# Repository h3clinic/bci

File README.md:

# BioGENEius Neural Signal Analysis Pipeline

## Model Details

| Field | Value |
|-------|-------|
| **Name** | BioGENEius Computational Pipeline v1 |
| **Version** | 1.0.0 |
| **Architecture** | Two-stage: Classical (CUSUM/RF) + Deep (NeuralQANet) |
| **Parameters** | 76,045 (Deep model) |
| **Framework** | PyTorch (CPU-only, no GPU required) |
| **License** | Research use only |

## Framing

> Artifact-resilient detection of suppression-like electrophysiological
> perturbation signatures under a low-cost phantom protocol.

**Key constraint:** We never claim neurons until we have biology.

## Intended Use

Detection and classification of electrophysiological perturbation signatures
in multichannel time-series data acquired from a low-cost phantom system.
Designed for competition demonstration and research prototyping.

### Primary Use Cases
- Detecting onset of suppression-like perturbations in phantom recordings
- Classifying perturbation cause (9 synthetic proxy classes)
- Quantifying detection latency and classification confidence
- Generating reproducible evaluation reports

### Out of Scope
- Clinical diagnosis or treatment decisions
- Real-time closed-loop neural interfaces
- Claims about biological neurotoxicity from proxy labels

## Pipeline Architecture

```
Acquire (frames → ADC → µV)
  ↓
QC / Artifact Segmentation (ML mask + quality score)
  ↓
Detect Change (CUSUM or z-score baseline comparison)
  ↓
Classify Cause (RF vs Deep model, 9-class + binary)
  ↓
Report (figures + latency + CI + confidence + "unknown" option)
```

### Stage 1 — Classical Detection
- **CUSUM** change-point detection on channel-averaged RMS
- **Z-score** alternative with sliding baseline window
- Outputs: detected (bool), detection latency (seconds), CUSUM statistic

### Stage 2 — Classical Classification
- **Random Forest** on 20 handcrafted features (RMS ratio, spectral entropy, band powers, etc.)
- Binary (perturbation vs baseline) + 9-class cause classification
- Wilson confidence intervals on all accuracy metrics

### Stage 3 — Deep Classification (NeuralQANet)
- 1D CNN backbone → attention pooling → 3 heads:
  - Artifact mask (binary per-sample)
  - Cause classification (9-class)
  - Severity regression (continuous 0–1)
- Self-supervised pretraining: masked reconstruction + NT-Xent contrastive loss
- 7 domain-randomization augmentations: 60Hz injection, channel dropout, gain jitter, coupling, drift, clipping, time mask
- Temperature-calibrated output probabilities

## Proxy Labels — What We Claim and What We Don't

All perturbation classes are **proxy signatures†**, not validated biological effects:

| Class | Proxy Signature | What It Actually Is |
|-------|-----------------|---------------------|
| Spike Suppression† | Reduced spike amplitude/rate | Synthetic amplitude modulation |
| Burst Collapse† | Loss of burst patterns | Synthetic burst removal |
| Spectral Shift† | Changed power spectrum | Synthetic PSD warping |
| Mixed Suppression† | Combined signatures | Multiple synthetic effects |
| Amplitude Modulation† | Gain changes | Synthetic scaling |
| Frequency Drift† | Center frequency shift | Synthetic frequency modulation |
| Baseline Drift† | DC offset wander | Synthetic drift injection |
| Coupling Change† | Inter-channel correlation shift | Synthetic coupling matrix |
| Artifact Injection† | Non-physiological transient | Synthetic artifact waveforms |

**†** = proxy label. Biological validation requires phantom recordings
with known perturbation agents under controlled conditions.

## Training Data

- **Source**: `analysis/perturbation_library.py` — deterministic synthetic generators
- **Classes**: 9 perturbation types + baseline
- **Severities**: 3 levels (0.3, 0.6, 0.9)
- **Channels**: 16 (configurable)
- **Sample rate**: 20 kHz (configurable)
- **Augmentations**: 7 domain-randomization transforms

**No real biological data was used for training or evaluation.**

## Evaluation Protocol

| Figure | What It Tests |
|--------|--------------|
| Fig 1 | Onset detection latency + false positive rate |
| Fig 2 | Cause classification confusion matrix + ROC |
| Fig 3 | Robustness under noise and artifact stress |
| Fig 4 | Ablation — why two-stage matters |
| Fig 5 | 3-way comparison: Classical vs RF vs Deep |
| Fig 6 | Stress grid: SNR × severity (where Deep beats Classical) |
| Fig 7 | Domain shift: train A / test B generalization |

### ML Earns Its Keep
- **Random noise floor**: ML does NOT beat physics. PCB shielding + analog design does.
- **Structured artifacts**: ML DOES help with 60Hz, coupling, drift, and other patterned contamination.
- Deep model must beat RF baseline to be included; RF must beat CUSUM to be included.

## Known Limitations

1. **Synthetic only** — All training/evaluation on synthetic perturbation library. No real data yet.
2. **Domain shift** — Performance may degrade when real phantom data differs from synthetic assumptions.
3. **Small model** — 76K params is deliberately small for CPU inference; may under-fit complex patterns.
4. **Temperature calibration** — Calibrated on synthetic validation set; re-calibrate on real data.
5. **Proxy labels** — No biological ground truth. Labels describe electrical signatures, not mechanisms.
6. **Single phantom protocol** — Validated only against BioGENEius Phantom Protocol v2.

## "Unknown" Behavior

When the model encounters data that doesn't match any trained class:
- Top-class probability drops below 0.3
- System flags as "low-confidence" in predictions.csv
- **Intended behavior: don't make a call when you don't know**

## Reproducibility

```bash
# One command. Generates everything.
python analysis/run_pipeline.py --source synthetic --seed 42

# Outputs to out/run_YYYYMMDD_HHMMSS/:
#   fig1–fig7 (PNG), predictions.csv, metrics.json, model_card.md
```

All random state is seeded. Same seed → same results.

## Ethical Considerations

- This system processes synthetic electrical signals, not human data
- No patient data, no clinical decisions, no diagnostic claims
- Proxy labels are clearly marked to prevent over-interpretation
- "Unknown" class prevents forced classification of novel patterns
- All code and evaluation are fully reproducible and auditable

## Citation

If referencing this work, please cite the BioGENEius competition entry
and note that all results are from synthetic simulation studies.

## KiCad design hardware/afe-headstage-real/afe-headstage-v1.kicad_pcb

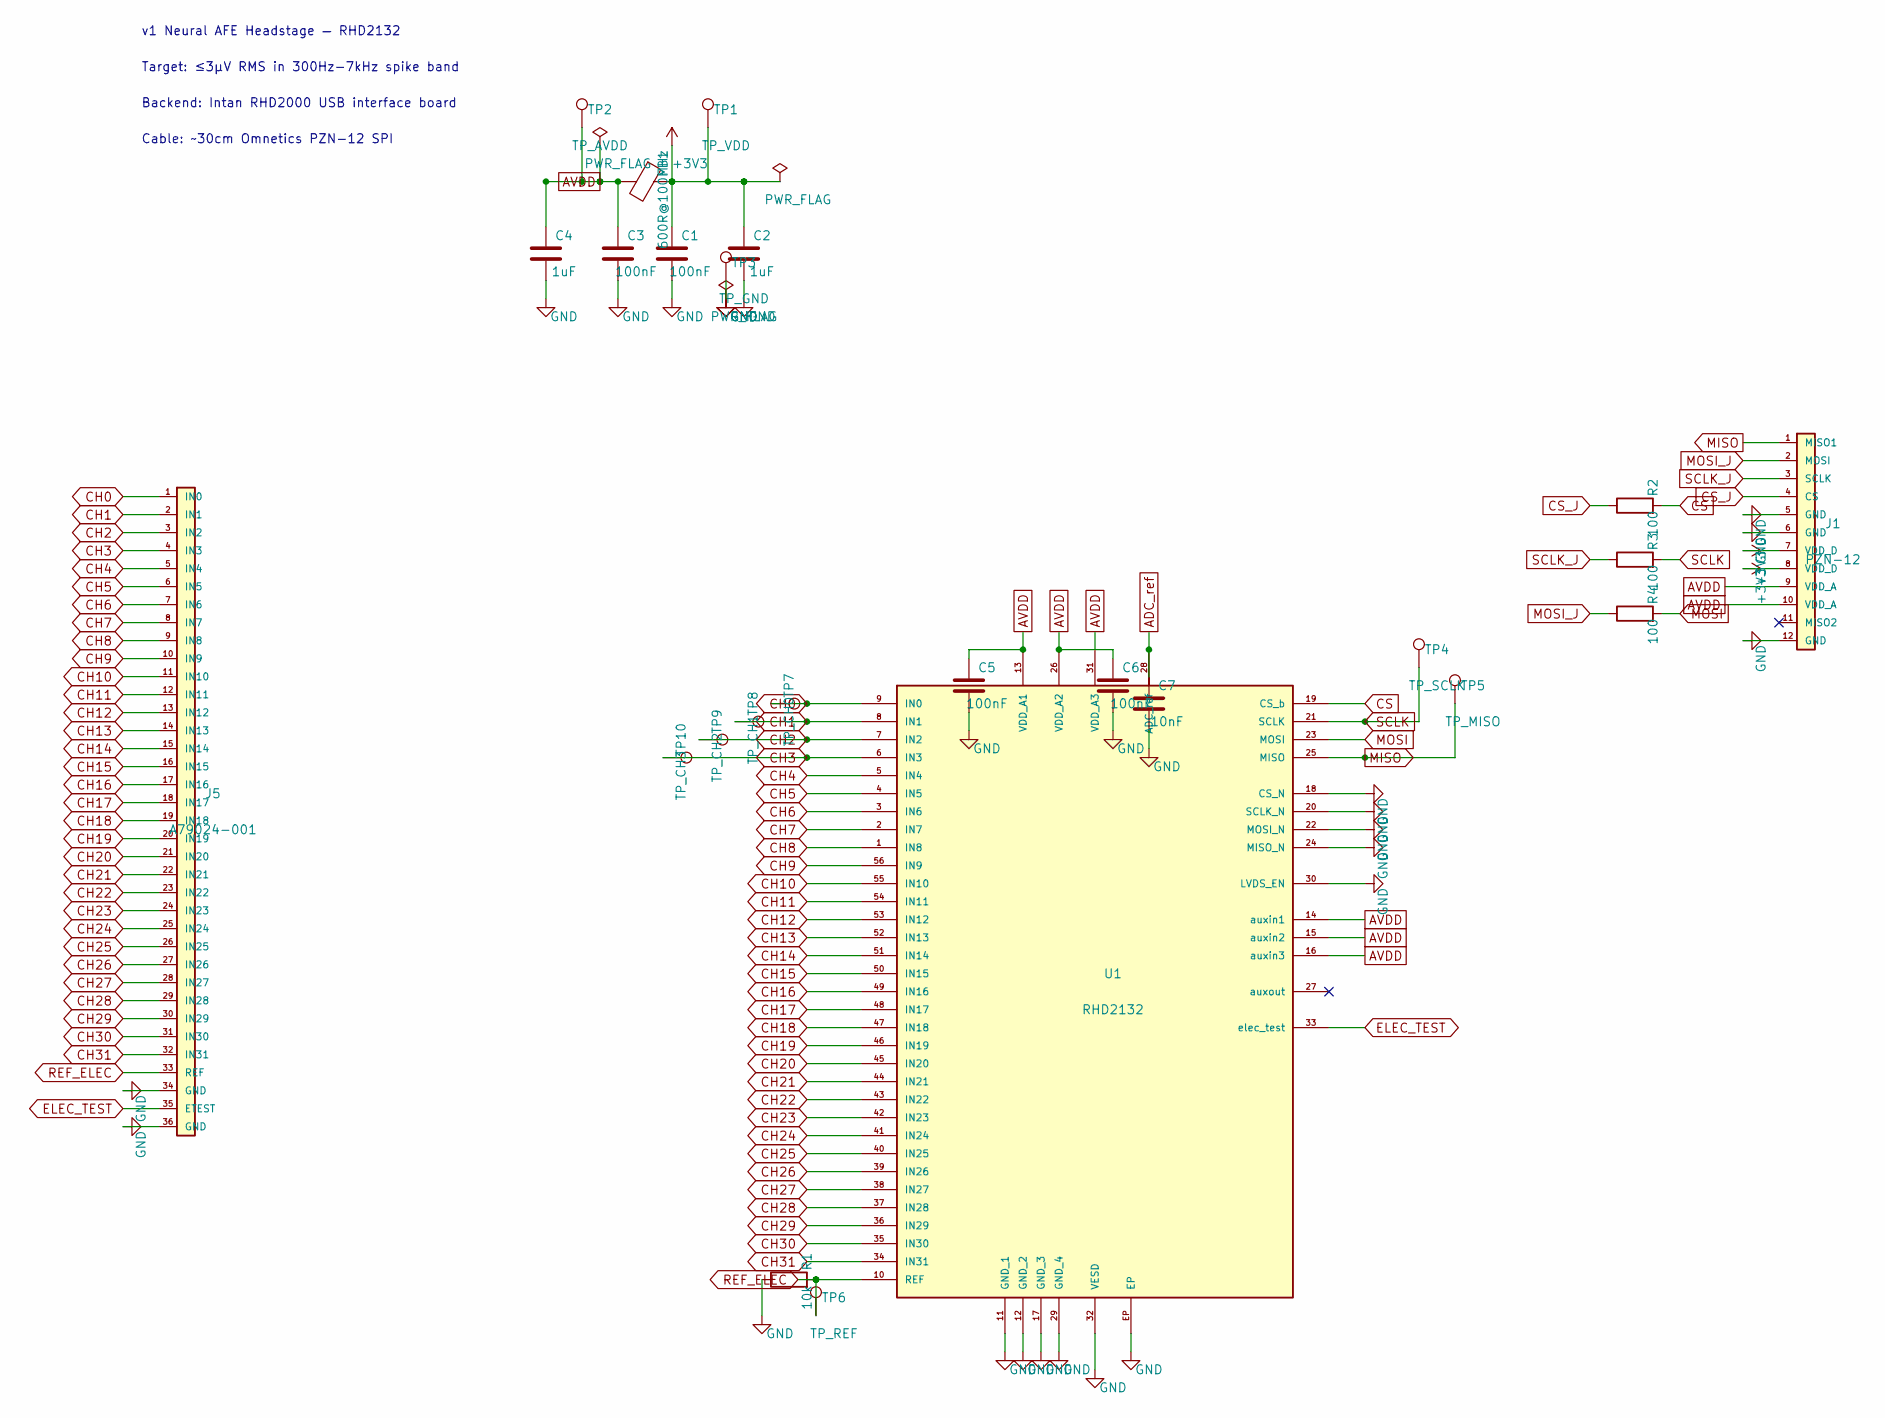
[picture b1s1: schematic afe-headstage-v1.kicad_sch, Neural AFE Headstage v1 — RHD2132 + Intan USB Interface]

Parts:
C1, C3, C5, C6: 100nF; R_0402_1005Metric
C2, C4: 1uF; R_0402_1005Metric
C7: 10nF; R_0402_1005Metric
FB1: 600R@100MHz; R_0402_1005Metric
J1: PZN-12; Omnetics_PZN-12-AA
J5: A79024-001; Omnetics_A79024_36pin
R1: 10k; R_0402_1005Metric
R2, R3, R4: 100; R_0402_1005Metric
TP1: TP_VDD; TestPoint_Pad_D1.0mm
TP2: TP_AVDD; TestPoint_Pad_D1.0mm
TP3: TP_GND; TestPoint_Pad_D1.0mm
TP4: TP_SCLK; TestPoint_Pad_D1.0mm
TP5: TP_MISO; TestPoint_Pad_D1.0mm
TP6: TP_REF; TestPoint_Pad_D1.0mm
TP7: TP_CH0; TestPoint_Pad_D1.0mm
TP8: TP_CH1; TestPoint_Pad_D1.0mm
TP9: TP_CH2; TestPoint_Pad_D1.0mm
TP10: TP_CH3; TestPoint_Pad_D1.0mm
U1: RHD2132; RHD2132_QFN56

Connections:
+3V3: C1.1, C2.1, FB1.1, J1.7 (VDD_D), J1.8 (VDD_D), TP1.1
ADC_ref: C7.1, U1.28 (ADC_ref)
AVDD: C3.1, C4.1, C5.1, C6.1, FB1.2, J1.9 (VDD_A), J1.10 (VDD_A), TP2.1, U1.13 (VDD_A1), U1.14 (auxin1), U1.15 (auxin2), U1.16 (auxin3), U1.26 (VDD_A2), U1.31 (VDD_A3)
CH0: J5.1 (IN0), TP7.1, U1.9 (IN0)
CH1: J5.2 (IN1), TP8.1, U1.8 (IN1)
CH2: J5.3 (IN2), TP9.1, U1.7 (IN2)
CH3: J5.4 (IN3), TP10.1, U1.6 (IN3)
CH4: J5.5 (IN4), U1.5 (IN4)
CH5: J5.6 (IN5), U1.4 (IN5)
CH6: J5.7 (IN6), U1.3 (IN6)
CH7: J5.8 (IN7), U1.2 (IN7)
CH8: J5.9 (IN8), U1.1 (IN8)
CH9: J5.10 (IN9), U1.56 (IN9)
CH10: J5.11 (IN10), U1.55 (IN10)
CH11: J5.12 (IN11), U1.54 (IN11)
CH12: J5.13 (IN12), U1.53 (IN12)
CH13: J5.14 (IN13), U1.52 (IN13)
CH14: J5.15 (IN14), U1.51 (IN14)
CH15: J5.16 (IN15), U1.50 (IN15)
CH16: J5.17 (IN16), U1.49 (IN16)
CH17: J5.18 (IN17), U1.48 (IN17)
CH18: J5.19 (IN18), U1.47 (IN18)
CH19: J5.20 (IN19), U1.46 (IN19)
CH20: J5.21 (IN20), U1.45 (IN20)
CH21: J5.22 (IN21), U1.44 (IN21)
CH22: J5.23 (IN22), U1.43 (IN22)
CH23: J5.24 (IN23), U1.42 (IN23)
CH24: J5.25 (IN24), U1.41 (IN24)
CH25: J5.26 (IN25), U1.40 (IN25)
CH26: J5.27 (IN26), U1.39 (IN26)
CH27: J5.28 (IN27), U1.38 (IN27)
CH28: J5.29 (IN28), U1.37 (IN28)
CH29: J5.30 (IN29), U1.36 (IN29)
CH30: J5.31 (IN30), U1.35 (IN30)
CH31: J5.32 (IN31), U1.34 (IN31)
CS: R2.2, U1.19 (CS_b)
CS_J: J1.4 (CS), R2.1
ELEC_TEST: J5.35 (ETEST), U1.33 (elec_test)
GND: C1.2, C2.2, C3.2, C4.2, C5.2, C6.2, C7.2, J1.5 (GND), J1.6 (GND), J1.12 (GND), J5.34 (GND), J5.36 (GND), R1.1, TP3.1, U1.11 (GND_1), U1.12 (GND_2), U1.17 (GND_3), U1.18 (CS_N), U1.20 (SCLK_N), U1.22 (MOSI_N), U1.24 (MISO_N), U1.29 (GND_4), U1.30 (LVDS_EN), U1.32 (VESD), U1.EP
MISO: J1.1 (MISO1), TP5.1, U1.25 (MISO)
MOSI: R4.2, U1.23 (MOSI)
MOSI_J: J1.2 (MOSI), R4.1
REF_ELEC: J5.33 (REF), R1.2, TP6.1, U1.10 (REF)
SCLK: R3.2, TP4.1, U1.21 (SCLK)
SCLK_J: J1.3 (SCLK), R3.1

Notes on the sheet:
v1 Neural AFE Headstage — RHD2132
Target: ≤3µV RMS in 300Hz-7kHz spike band
Backend: Intan RHD2000 USB interface board
Cable: ~30cm Omnetics PZN-12 SPI

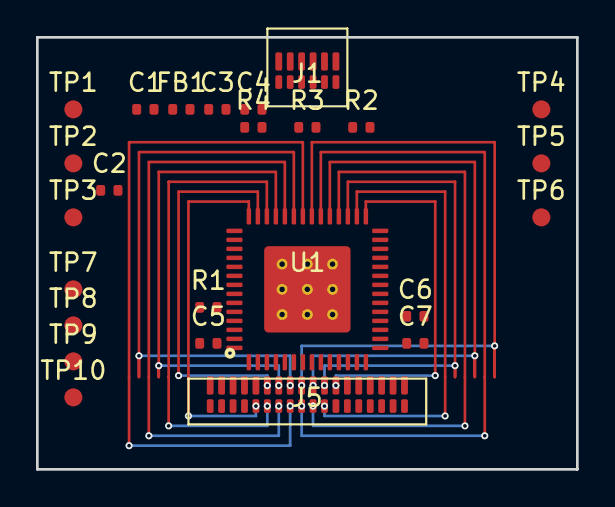
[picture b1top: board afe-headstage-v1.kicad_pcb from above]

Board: 4 copper layers, 30.0 x 24.0 mm, 25 parts (0 on the bottom side), 45 nets.

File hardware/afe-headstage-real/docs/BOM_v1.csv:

Ref,Qty,Value,Package,Description,MPN,Supplier,Notes
U1,1,RHD2132,QFN-56 (8x8mm),32-ch neural AFE with on-chip ADC,RHD2132,Intan Technologies,0.5mm pitch; EP 4.8x4.8mm; CMOS SPI mode
J1,1,PZN-12-AA,Omnetics PZN-12,"12-pin polarized nano, SPI cable connector",PZN-12-AA,Omnetics,Mates with Intan RHD2000 USB interface board cable
J5,1,A79024-001,Omnetics A79024,"36-pin nano-strip, electrode connector",A79024-001,Omnetics,0.635mm pitch; dual-row SMD
FB1,1,600R@100MHz,0402,Ferrite bead for analog supply filtering,BLM15AG601SN1D,Murata,AVDD/DVDD isolation
C1,1,100nF,0402,+3V3 bypass (near power entry),GRM155R71C104KA88D,Murata,X7R 16V
C2,1,1uF,0402,+3V3 bulk (near power entry),GRM155R61A105KE01D,Murata,X5R 10V
C3,1,100nF,0402,AVDD bypass (near FB1 output),GRM155R71C104KA88D,Murata,X7R 16V
C4,1,1uF,0402,AVDD bulk (near FB1 output),GRM155R61A105KE01D,Murata,X5R 10V
C5,1,100nF,0402,VDD bypass near U1 pin 13,GRM155R71C104KA88D,Murata,X7R 16V; <1mm from VDD1
C6,1,100nF,0402,VDD bypass near U1 pin 26,GRM155R71C104KA88D,Murata,X7R 16V; <1mm from VDD2
C7,1,10nF,0402,ADC_ref decoupling,GRM155R71H103KA88D,Murata,X7R 50V; <5mm from U1 pin 28
R1,1,10k,0402,REF electrode bias to GND,RC0402FR-0710KL,Yageo,1% tolerance
R2,1,100R,0402,SPI series — CS line,RC0402FR-07100RL,Yageo,1%; damps cable ringing per Intan ref
R3,1,100R,0402,SPI series — SCLK line,RC0402FR-07100RL,Yageo,1%; damps cable ringing per Intan ref
R4,1,100R,0402,SPI series — MOSI line,RC0402FR-07100RL,Yageo,1%; damps cable ringing per Intan ref
TP1,1,TP_VDD,1.0mm pad,Test point +3V3,5000,Keystone,Solder pad only
TP2,1,TP_AVDD,1.0mm pad,Test point AVDD,5000,Keystone,Solder pad only
TP3,1,TP_GND,1.0mm pad,Test point GND,5000,Keystone,Solder pad only
TP4,1,TP_CH0,1.0mm pad,Test point CH0,5000,Keystone,Solder pad only
TP5,1,TP_CH1,1.0mm pad,Test point CH1,5000,Keystone,Solder pad only
TP6,1,TP_CH2,1.0mm pad,Test point CH2,5000,Keystone,Solder pad only
TP7,1,TP_CH3,1.0mm pad,Test point CH3,5000,Keystone,Solder pad only
TP8,1,TP_SCLK,1.0mm pad,Test point SCLK,5000,Keystone,Solder pad only
TP9,1,TP_MISO,1.0mm pad,Test point MISO,5000,Keystone,Solder pad only

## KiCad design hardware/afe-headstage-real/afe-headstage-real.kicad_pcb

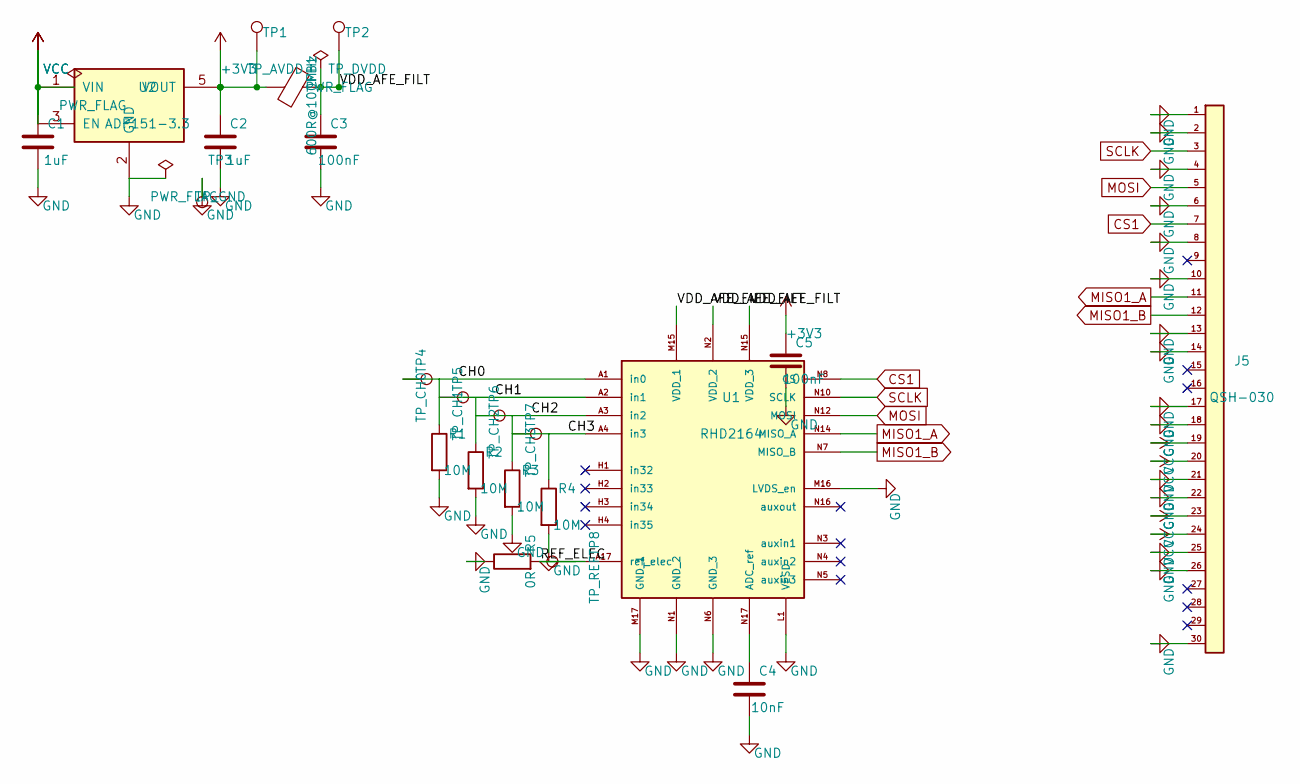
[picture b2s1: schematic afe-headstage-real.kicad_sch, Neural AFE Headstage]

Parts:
C1, C2: 1uF
C3, C5: 100nF
C4: 10nF
FB1: 600R@100MHz
J5: QSH-030
R1, R2, R3, R4: 10M
R5: 0R
TP1: TP_AVDD
TP2: TP_DVDD
TP3: TP_GND
TP4: TP_CH0
TP5: TP_CH1
TP6: TP_CH2
TP7: TP_CH3
TP8: TP_REF
U1: RHD2164
U2: ADP151-3.3

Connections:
+3V3: C2.1, C5.1, FB1.2, TP1.1, U2.5 (VOUT)
/CH0: R1.1, TP4.1, U1.A1 (in0)
/CH1: R2.1, TP5.1, U1.A2 (in1)
/CH2: R3.1, TP6.1, U1.A3 (in2)
/CH3: R4.1, TP7.1, U1.A4 (in3)
/REF_ELEC: R5.2, TP8.1, U1.A17 (ref_elec)
/VDD_AFE_FILT: C3.1, FB1.1, TP2.1, U1.M15 (VDD_1), U1.N2 (VDD_2), U1.N15 (VDD_3)
CS1: J5.7 (CS1), U1.N8 (CS)
GND: C1.2, C2.2, C3.2, C4.2, C5.2, J5.1 (GND), J5.2 (GND), J5.4 (GND), J5.6 (GND), J5.8 (GND), J5.10 (GND), J5.13 (GND), J5.14 (GND), J5.17 (GND), J5.18 (GND), J5.21 (GND), J5.22 (GND), J5.25 (GND), J5.26 (GND), J5.30 (GND), R1.2, R2.2, R3.2, R4.2, R5.1, TP3.1, U1.L1 (VESD), U1.M16 (LVDS_en), U1.M17 (GND_1), U1.N1 (GND_2), U1.N6 (GND_3), U2.2 (GND)
MISO1_A: J5.11 (MISO1_A), U1.N14 (MISO_A)
MISO1_B: J5.12 (MISO1_B), U1.N7 (MISO_B)
MOSI: J5.5 (MOSI), U1.N12 (MOSI)
unnamed: C4.1, U1.N17 (ADC_ref)
SCLK: J5.3 (SCLK), U1.N10 (SCLK)
VCC: C1.1, J5.19 (VIN), J5.20 (VIN), J5.23 (VIN), J5.24 (VIN), U2.1 (VIN), U2.3 (EN)

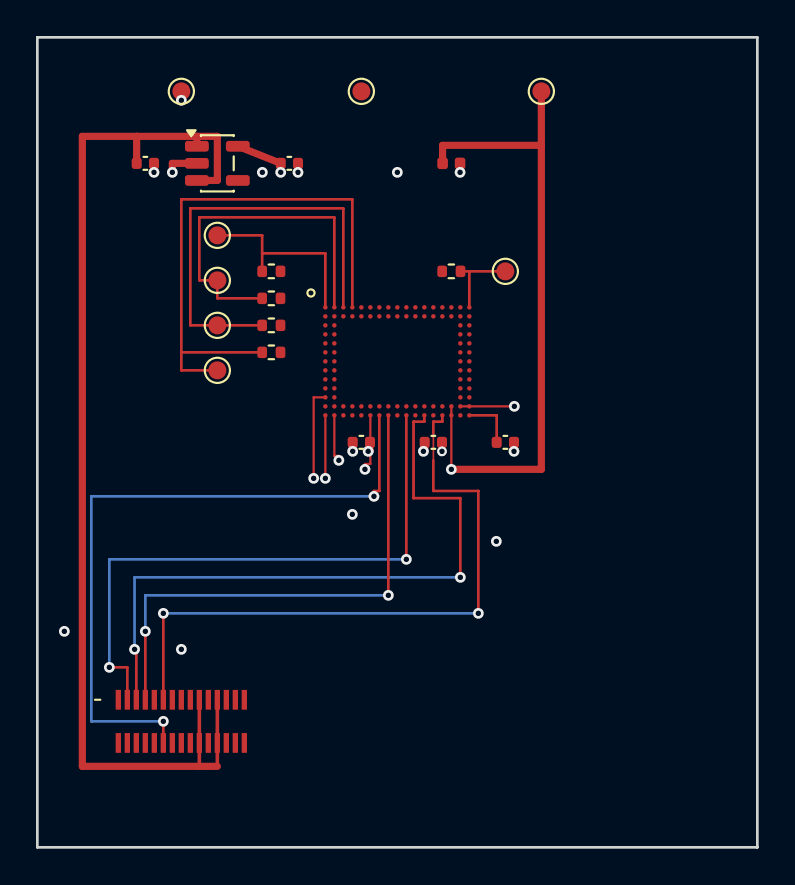
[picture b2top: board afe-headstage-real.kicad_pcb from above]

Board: 4 copper layers, 40.0 x 45.0 mm, 22 parts (0 on the bottom side), 15 nets.

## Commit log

2026-03-27 Add new file 'first' with initial content
2026-03-27 uploaded the files
2026-03-27 Add model card for BioGENEius pipeline
    Add detailed model card for BioGENEius Neural Signal Analysis Pipeline, including model details, intended use, pipeline architecture, training data, evaluation protocol, known limitations, and ethica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
